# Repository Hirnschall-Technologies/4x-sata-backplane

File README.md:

## Custom 4x SATA Backplane for home-nas and servers
If you are interested in the design process behind this pcb, take a look at [this accompanying blog post.](https://blog.hirnschall.net/4x-sata-backplane)

### Why use a backplane
Using a backplane allows multiple disks to be connected to a single power-supply cable. For this a 4-pin molex connector is used as it can sustain the spinup current of 4 disks.

### How to order    
Download the the latest gerber-files from the [release tab](https://github.com/shirnschall/4x-sata-backplane/releases). Order then on e.g. jlcpcb.com.     
Use the following settings when ordering:
- PCB thickness: 1.6mm
- Layers: 4
- Impedance Control: yes, JLC04161H-7628
- Material type: FR4-Standard TG 135-140
- Copper weight: 1oz outer, 0.5oz inner
- Remove Order Number: Specify a location (remove if you want to)

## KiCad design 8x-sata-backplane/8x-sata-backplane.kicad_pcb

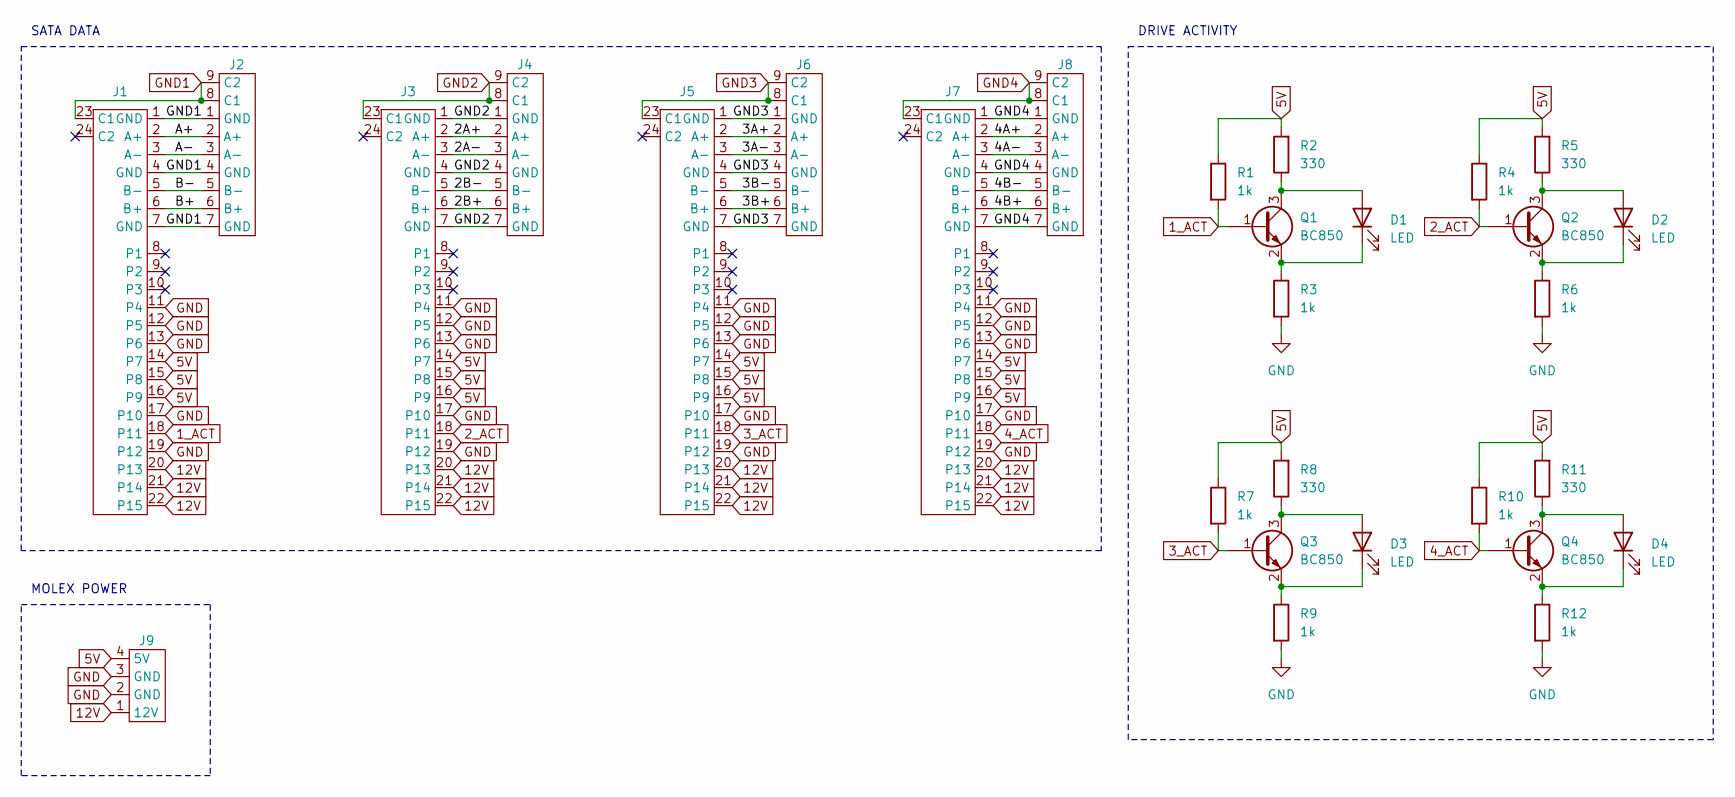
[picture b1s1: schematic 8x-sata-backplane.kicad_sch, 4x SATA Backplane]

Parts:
D1, D2, D3, D4: LED; LED_0603_1608Metric
J1, J3, J5, J7: sata-backplane-connector-vert
J2, J4, J6, J8: sata-data-connector
J9: 4-pin-molex-hdd
Q1, Q2, Q3, Q4: BC850; SOT-23
R1, R3, R4, R6, R7, R9, R10, R12: 1k; R_0805_2012Metric
R2, R5, R8, R11: 330; R_0805_2012Metric

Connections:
1_ACT: J1.18 (P11), Q1.1 (B), R1.2
2_ACT: J3.18 (P11), Q2.1 (B), R4.2
3_ACT: J5.18 (P11), Q3.1 (B), R7.2
4_ACT: J7.18 (P11), Q4.1 (B), R10.2
5V: J1.14 (P7), J1.15 (P8), J1.16 (P9), J3.14 (P7), J3.15 (P8), J3.16 (P9), J5.14 (P7), J5.15 (P8), J5.16 (P9), J7.14 (P7), J7.15 (P8), J7.16 (P9), J9.4 (5V), R1.1, R2.2, R4.1, R5.2, R7.1, R8.2, R10.1, R11.2
12V: J1.20 (P13), J1.21 (P14), J1.22 (P15), J3.20 (P13), J3.21 (P14), J3.22 (P15), J5.20 (P13), J5.21 (P14), J5.22 (P15), J7.20 (P13), J7.21 (P14), J7.22 (P15), J9.1 (12V)
/2A+: J3.2 (A+), J4.2 (A+)
/2A-: J3.3 (A-), J4.3 (A-)
/2B+: J3.6 (B+), J4.6 (B+)
/2B-: J3.5 (B-), J4.5 (B-)
/3A+: J5.2 (A+), J6.2 (A+)
/3A-: J5.3 (A-), J6.3 (A-)
/3B+: J5.6 (B+), J6.6 (B+)
/3B-: J5.5 (B-), J6.5 (B-)
/4A+: J7.2 (A+), J8.2 (A+)
/4A-: J7.3 (A-), J8.3 (A-)
/4B+: J7.6 (B+), J8.6 (B+)
/4B-: J7.5 (B-), J8.5 (B-)
/A+: J1.2 (A+), J2.2 (A+)
/A-: J1.3 (A-), J2.3 (A-)
/B+: J1.6 (B+), J2.6 (B+)
/B-: J1.5 (B-), J2.5 (B-)
GND: J1.11 (P4), J1.12 (P5), J1.13 (P6), J1.17 (P10), J1.19 (P12), J3.11 (P4), J3.12 (P5), J3.13 (P6), J3.17 (P10), J3.19 (P12), J5.11 (P4), J5.12 (P5), J5.13 (P6), J5.17 (P10), J5.19 (P12), J7.11 (P4), J7.12 (P5), J7.13 (P6), J7.17 (P10), J7.19 (P12), J9.2 (GND), J9.3 (GND), R3.2, R6.2, R9.2, R12.2
GND1: J1.1 (GND), J1.4 (GND), J1.7 (GND), J1.23 (C1), J2.1 (GND), J2.4 (GND), J2.7 (GND), J2.8 (C1), J2.9 (C2)
GND2: J3.1 (GND), J3.4 (GND), J3.7 (GND), J3.23 (C1), J4.1 (GND), J4.4 (GND), J4.7 (GND), J4.8 (C1), J4.9 (C2)
GND3: J5.1 (GND), J5.4 (GND), J5.7 (GND), J5.23 (C1), J6.1 (GND), J6.4 (GND), J6.7 (GND), J6.8 (C1), J6.9 (C2)
GND4: J7.1 (GND), J7.4 (GND), J7.7 (GND), J7.23 (C1), J8.1 (GND), J8.4 (GND), J8.7 (GND), J8.8 (C1), J8.9 (C2)
unnamed: D1.2 (A), Q1.3 (C), R2.1
unnamed: D1.1 (K), Q1.2 (E), R3.1
unnamed: D2.2 (A), Q2.3 (C), R5.1
unnamed: D2.1 (K), Q2.2 (E), R6.1
unnamed: D3.2 (A), Q3.3 (C), R8.1
unnamed: D3.1 (K), Q3.2 (E), R9.1
unnamed: D4.2 (A), Q4.3 (C), R11.1
unnamed: D4.1 (K), Q4.2 (E), R12.1

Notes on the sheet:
DRIVE ACTIVITY
SATA DATA
MOLEX POWER

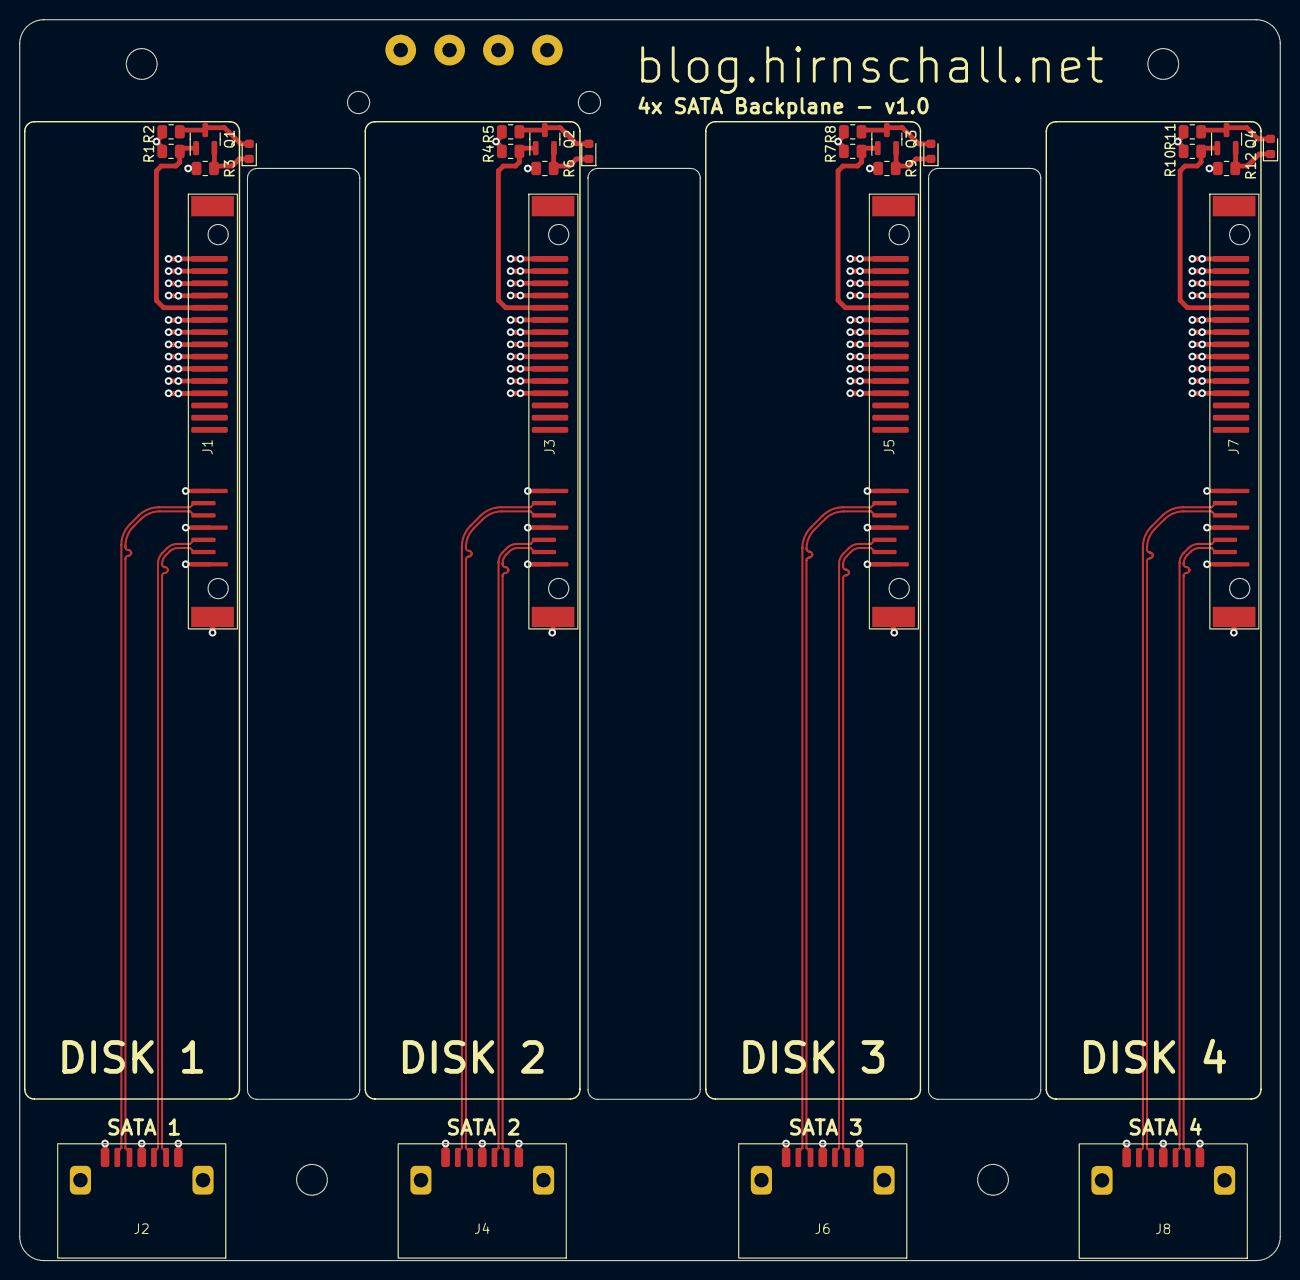
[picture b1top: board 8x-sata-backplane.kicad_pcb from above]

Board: 4 copper layers, 131.0 x 129.0 mm, 29 parts (1 on the bottom side), 35 nets.

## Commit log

2024-03-25 initial design of v1.0
2024-03-31 v1.0
2024-05-07 v1.0 html bom
2024-05-12 inital test of disk shape and spacing for cage
2026-03-30 update link to point to working post
2026-04-04 kicad mechanical step export
2026-04-06 add updated step files for drive cage, and pcb step export
